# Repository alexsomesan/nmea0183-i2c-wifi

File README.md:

# NMEA0183 WiFi bridge for NASA Clipper Wind instrument

Reads wind data from a NASA Clipper wind instrument via I2C and sends out NMEA0183 wind messages via WiFi.

# Hardware needed

At the very minimum, a prototype can be assembled with just an ESP32 dev board and a 5 pin DIN plug, by connecting the I2C and power lines from the connector directly to the board. The NASA unit output 5V level I2c, but ESP32 is 5V tolerrant so a level converter is not mandatory (still nice though).

[TODO: add pinnout diagram]

```
ESP32         < --- >  NASA 5 Pin DIN connector
-----------------------------------------------
GPIO21 (SDA)  < --- >  PIN 3
GPIO22 (SCL)  < --- >  PIN 1
GND           < --- >  PIN 2
```

The hardware folder contains an untested design (KiCAD 5) for an integrted board with power regulators and level shifters, which should give the most robust solution.

# Installation

To build the code, you need to install the official Espressif SDK, as explained here: https://docs.espressif.com/projects/esp-idf/en/latest/esp32/get-started/#installation-step-by-step

With the ESP-IDF successfully installed, connect the ESP32 board via USB and flash it with the following command:
```
idf.py partition_table-flash flash
```

Once that completes without erros, the board is ready to use. You need to connect it to a WiFi network (e.g. and OpenPlotter WiFi network).

To setup wifi, the board starts it's own WiFi network called "nasa-clipper-wind". Connect to that and wait for the login pop-up to show up. In the pop-up window you will be able to browse available networks and connect to the network of your choice. Once setup, the board will remember this network and connect to it on startup.

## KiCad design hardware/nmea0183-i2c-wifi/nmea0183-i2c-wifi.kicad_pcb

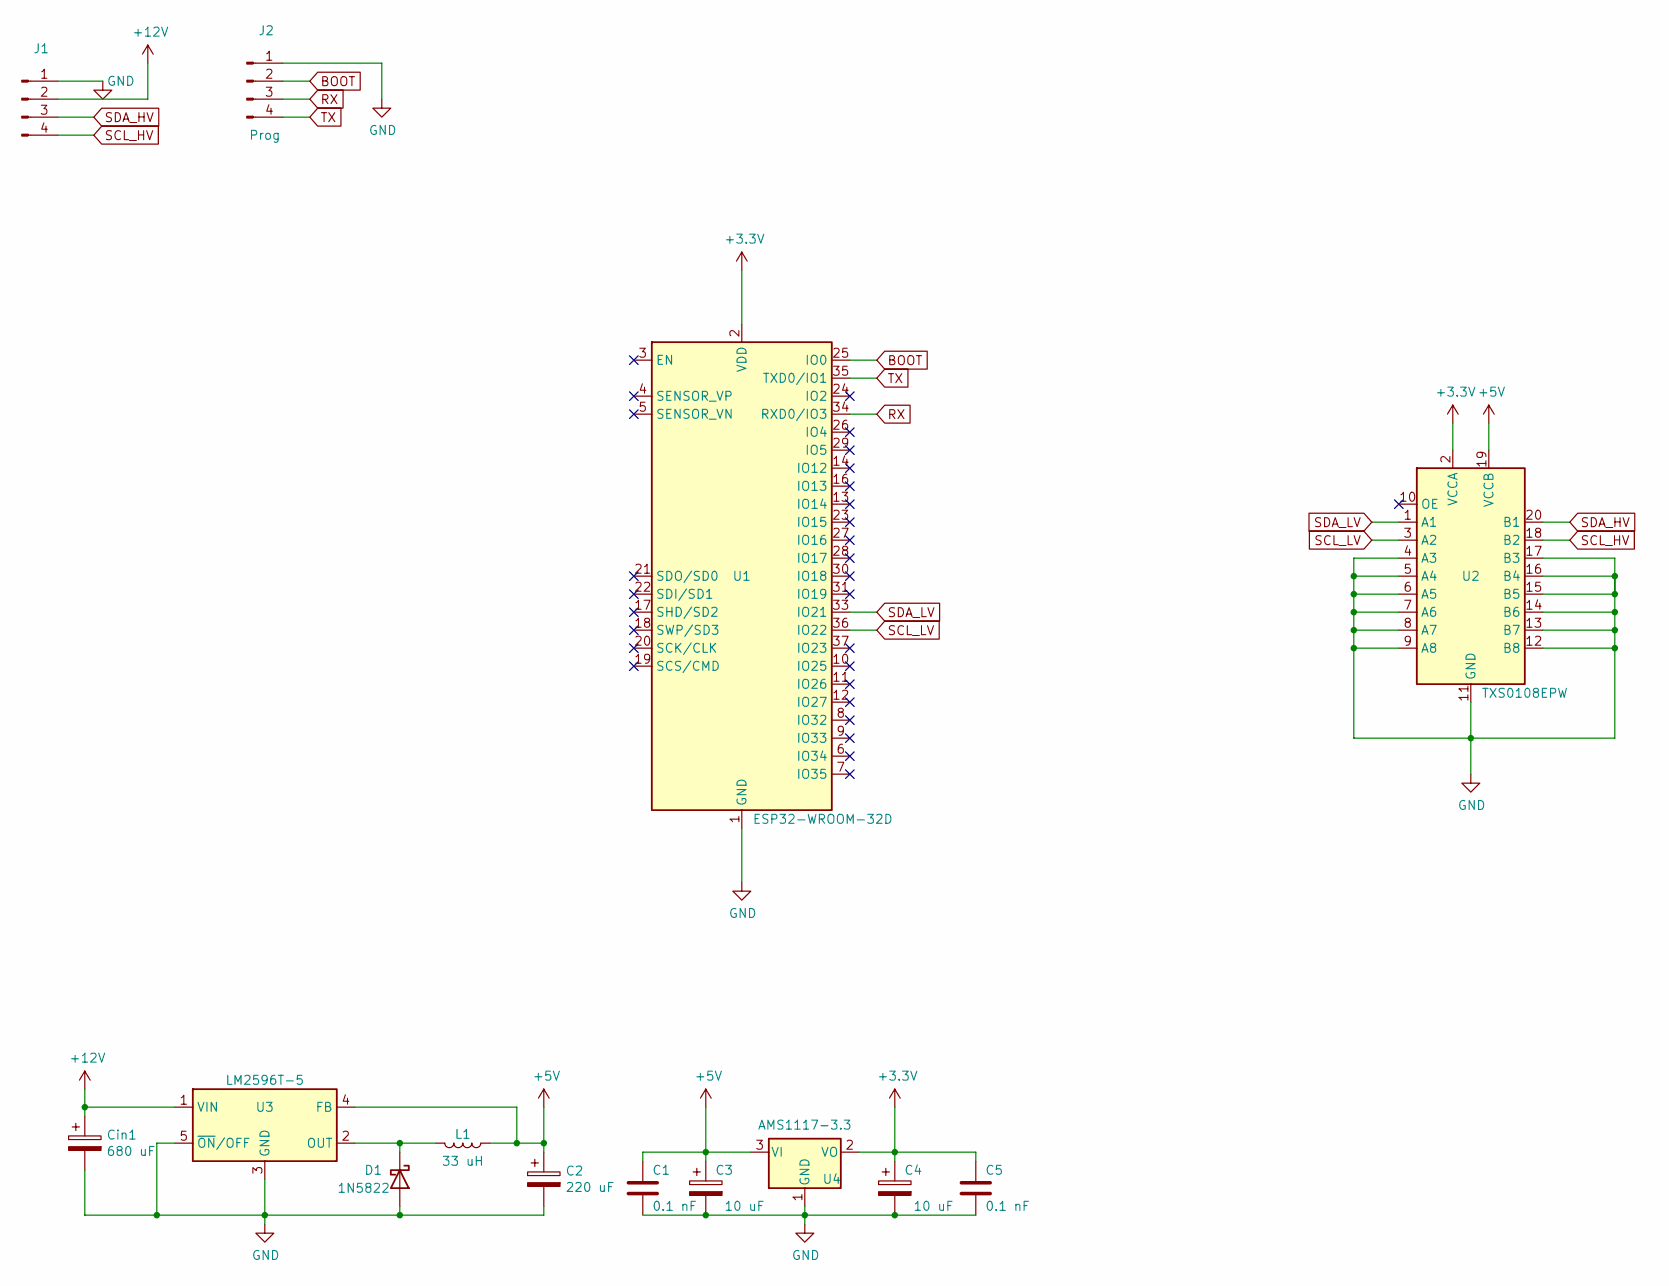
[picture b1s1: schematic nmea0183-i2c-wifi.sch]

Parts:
C1, C5: 0.1 nF; C_0805_2012Metric
C2: 220 uF; CP_Radial_D6.3mm_P2.50mm
C3, C4: 10 uF; CP_Radial_D4.0mm_P2.00mm
Cin1: 680 uF; CP_Radial_D10.0mm_P5.00mm
D1: 1N5822; D_DO-201AD_P15.24mm_Horizontal
J1: Conn_01x04_Male; JST_XH_B4B-XH-AM_1x04_P2.50mm_Vertical
J2: Prog; PinHeader_1x04_P2.54mm_Vertical
L1: 33 uH; L_Radial_D9.5mm_P5.00mm_Fastron_07HVP
U1: ESP32-WROOM-32D; ESP32-WROOM-32
U2: TXS0108EPW; TSSOP-20_4.4x6.5mm_P0.65mm
U3: LM2596T-5; TO-220-5_P3.4x3.7mm_StaggerOdd_Lead3.8mm_Vertical
U4: AMS1117-3.3; SOT-223-3_TabPin2

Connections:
+3V3: C4.1, C5.1, U1.2 (VDD), U2.2 (VCCA), U4.2 (VO)
+5V: C1.1, C2.1, C3.1, L1.1, U2.19 (VCCB), U3.4 (FB), U4.3 (VI)
+12V: Cin1.1, J1.2, U3.1 (VIN)
BOOT: J2.2, U1.25 (IO0)
GND: C1.2, C2.2, C3.2, C4.2, C5.2, Cin1.2, D1.2 (A), J1.1, J2.1, U1.1 (GND), U1.15 (GND), U1.38 (GND), U1.39 (GND), U2.4 (A3), U2.5 (A4), U2.6 (A5), U2.7 (A6), U2.8 (A7), U2.9 (A8), U2.11 (GND), U2.12 (B8), U2.13 (B7), U2.14 (B6), U2.15 (B5), U2.16 (B4), U2.17 (B3), U3.3 (GND), U3.5 (~ON~/OFF), U4.1 (GND)
unnamed: D1.1 (K), L1.2, U3.2 (OUT)
RX: J2.3, U1.34 (RXD0/IO3)
SCL_HV: J1.4, U2.18 (B2)
SCL_LV: U1.36 (IO22), U2.3 (A2)
SDA_HV: J1.3, U2.20 (B1)
SDA_LV: U1.33 (IO21), U2.1 (A1)
TX: J2.4, U1.35 (TXD0/IO1)

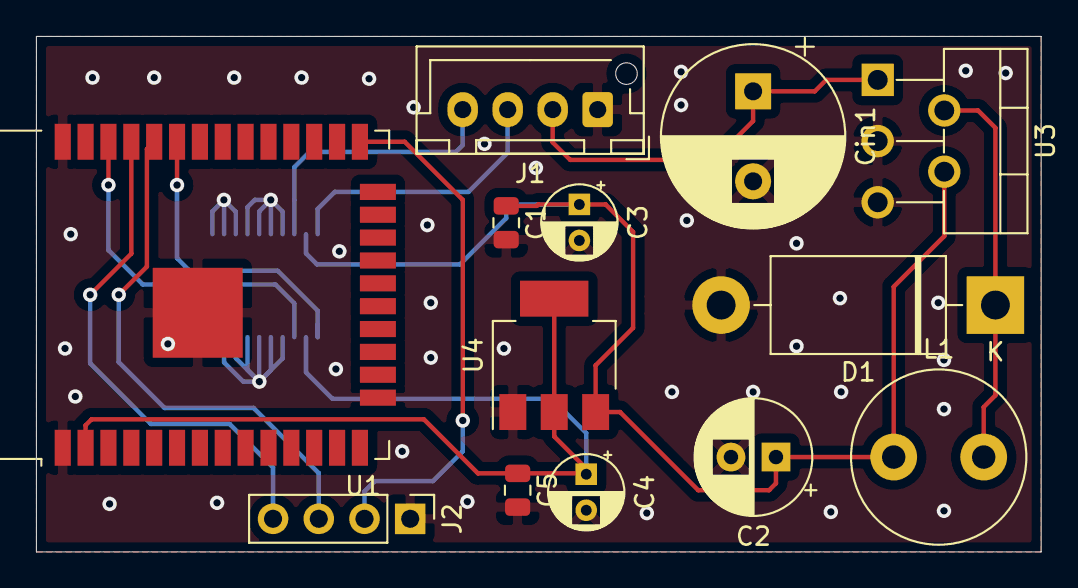
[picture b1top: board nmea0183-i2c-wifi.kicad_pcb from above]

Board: 2 copper layers, 55.8 x 28.6 mm, 14 parts (1 on the bottom side), 12 nets.

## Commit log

2020-09-04 Format NMEA sentence
2020-09-04 I2C receive works
2020-09-04 WiFi connects
2020-09-09 Move I2C pins and better check for receive errors
2020-09-09 WIP hardware design
2020-09-10 Initial working prototype - RTOS tasks for reading I2C and printing NMEA to log.
2020-09-10 UDP broadcast works
2020-09-10 Minimal hardware board
2021-05-11 Some readme updates
2021-05-11 Installation instructions
2021-05-11 Connection instructions
